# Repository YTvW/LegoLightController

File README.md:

# QBee LED Controller

A LEGO-stud-compatible LED controller board (Rev 1.0) built around the ATSAMD11C14A,
powered over USB-C. It drives up to two WS2812B (NeoPixel) strips and three
single-color LED channels.

## Hardware overview

| Part | Function |
|---|---|
| U1 — ATSAMD11C14A (SOIC-14) | MCU, 16KB flash / 4KB RAM, native USB |
| U2 — AP2111H-3.3 | 3.3V LDO for the MCU |
| P1 — USB-C (USB4110) | Power (5V) + USB 2.0 data; 5.1k CC pulldowns identify the board as a power sink |
| Q1–Q3 — BC847 | Low-side switches for the three LED channels (1k base, 10k pulldown) |
| R10, R11 — 470Ω | Series resistors on the WS2812B data lines |

### Connectors / IO

| Connector | Pads | Signal | MCU pin | Arduino pin |
|---|---|---|---|---|
| J1 | 1: +5V, 2: switched GND | LED1 channel | PA02 | 2 |
| J2 | 1: +5V, 2: switched GND | LED2 channel | PA04 | 4 |
| J3 | 1: +5V, 2: switched GND | LED3 channel | PA05 | 5 |
| J4 | 1: +5V, 2: data, 3: GND | WS2812B strip (DL1) | PA14 | 14 |
| J5 | 1: +5V, 2: data, 3: GND | WS2812B strip (DL2) | PA15 | 15 |
| J7 | 1: 3V3, 2: RESET, 3: SWCLK, 4: SWDIO, 5: NC, 6: GND | SWD programming header (DNP) | PA28/PA30/PA31 | — |
| TP1 | test point | EXT1 spare GPIO | PA08 | 8 |
| TP2 | test point | EXT2 spare GPIO | PA09 | 9 |

The LED channels (J1–J3) switch the LED's ground side through a transistor:
connect an LED (with its own series resistor if needed) between pad 1 (+5V)
and pad 2. A HIGH on the MCU pin turns the channel on.

Notes per pin:

- **PA02 (LED1, pin 2)** has no timer output — hardware PWM is not possible.
  `analogWrite()` on this pin uses the true 10-bit DAC; the transistor makes
  this behave as a crude analog dimmer only. Prefer channels LED2/LED3 for
  smooth PWM dimming.
- **PA04/PA05 (LED2/LED3)** have TC1 waveform outputs (WO0/WO1) — used by
  `pwm_driver` channels 0 and 1.
- **PA14/PA15 (strips)** also carry TC1 outputs; do not `analogWrite()` them.

## Arduino environment setup

1. Install the [Arduino IDE](https://www.arduino.cc/en/software) (2.x).
2. Add the Fab SAM core: **File → Preferences → Additional boards manager URLs**:

   ```
   https://raw.githubusercontent.com/qbolsee/ArduinoCore-fab-sam/master/json/package_Fab_SAM_index.json
   ```

3. **Tools → Board → Boards Manager**, search "Fab SAM", install
   **Fab SAM core for Arduino** (this project was built with 1.12.0).
4. Select **Tools → Board → Fab SAM boards → Generic D11C14A**.

### Board settings (Tools menu)

| Setting | Value | Notes |
|---|---|---|
| Clock Source | `INTERNAL_USB_CALIBRATED_OSCILLATOR` | Crystalless; calibrates 48MHz from USB. Switch to `INTERNAL_OSCILLATOR` if USB is disabled. |
| Bootloader Size | `4KB_BOOTLOADER` | Leaves 12KB for the application |
| Serial Config | `NO_UART_ONE_WIRE_ONE_SPI` | Saves ~1.5KB vs the default; USB `Serial` still works. The hardware UART (`Serial1`) is not wired to anything on this board. |
| USB Config | `CDC_ONLY` | Needed for `Serial` debugging and one-click uploads |
| Float | default | |
| Timer PWM Frequency | default (732.4Hz) | Only affects `analogWrite()` |

### Uploading

Normal uploads go over USB via the SAM-BA bootloader: just press Upload —
the IDE opens the port at 1200 baud to reset the board into the bootloader
automatically (this requires the running sketch to have USB CDC enabled).

If the chip is blank, or the sketch was built without CDC, flash via the SWD
pads (J7) with a CMSIS-DAP programmer and
[edbg](https://github.com/ataradov/edbg), or use the IDE's
*Burn Bootloader* with the Fab programmer selected. Once the bootloader is
on, USB uploads work as above.

## Firmware (`QBee Software/QBeeFirmware`)

| File | Purpose |
|---|---|
| `QBeeFirmware.ino` | Main sketch |
| `ws2812b_dma_driver.c/h` | WS2812B driver using **TCC0** PWM + DMA. Non-blocking: `ws2812b_show()` starts a hardware transfer and returns immediately. Uses TCC0's double-buffered `CCB` compare register so bit timing is glitch-free and immune to interrupts/USB load. |
| `pwm_driver.c/h` | LED-channel PWM using **TC1** (channels 0/1 → pins 4/5). TC2 exists but its outputs land on the SWD pins only. Costs no flash while unused (linker GC). |
| `neopixel_driver.c/h` | Older bit-banged WS2812B driver (blocks with interrupts off; superseded by the DMA driver) |

### Timer budget

| Peripheral | Owner |
|---|---|
| TCC0 | `ws2812b_dma_driver` (do not combine with `analogWrite`/`pwm_driver` on TCC0 pins) |
| TC1 | `pwm_driver` channels 0/1 (pins 4/5). Also claimed by `tone()` — don't use both. |
| TC2 | `pwm_driver` channels 2/3 — outputs only on SWD pins PA30/PA31, effectively unusable |
| SysTick | `millis()`/`micros()`/`delay()` (not a shared peripheral) |
| DMAC ch 0 | `ws2812b_dma_driver` |

### Flash budget

The app space is 12288 bytes. Measured levers if space runs out:

| Change | Approx. saving |
|---|---|
| Serial Config → `NO_UART...` | 1.5KB (free — `Serial1` unused) |
| USB Config → `WITHOUT_CDC` (drop `Serial` prints) | +2KB |
| USB Config → `USB_DISABLED` (also set Clock → `INTERNAL_OSCILLATOR`) | +4KB more |
| Bootloader → `NO_BOOTLOADER` (SWD uploads only) | +4KB of app space |

## Known hardware issues (Rev 1.0)

- **No level shifter on the WS2812B data lines.** Data is 3.3V while the
  strip runs at 5V; the strip's VIH spec is 0.7×VDD = 3.5V, so operation
  relies on real-world margin. Symptom: strips work on a USB-C wall supply
  but fail or glitch on some PC ports (slightly higher/noisier VBUS).
  Workaround: a silicon diode in series with the strip's +5V feed (drops
  strip VDD to ~4.4V). Proper fix for Rev 2: a 74AHCT1G125 / SN74LV1T125
  buffer on each data line, powered from 5V.
- **LED1 (PA02) has no hardware PWM** — see pin notes above.

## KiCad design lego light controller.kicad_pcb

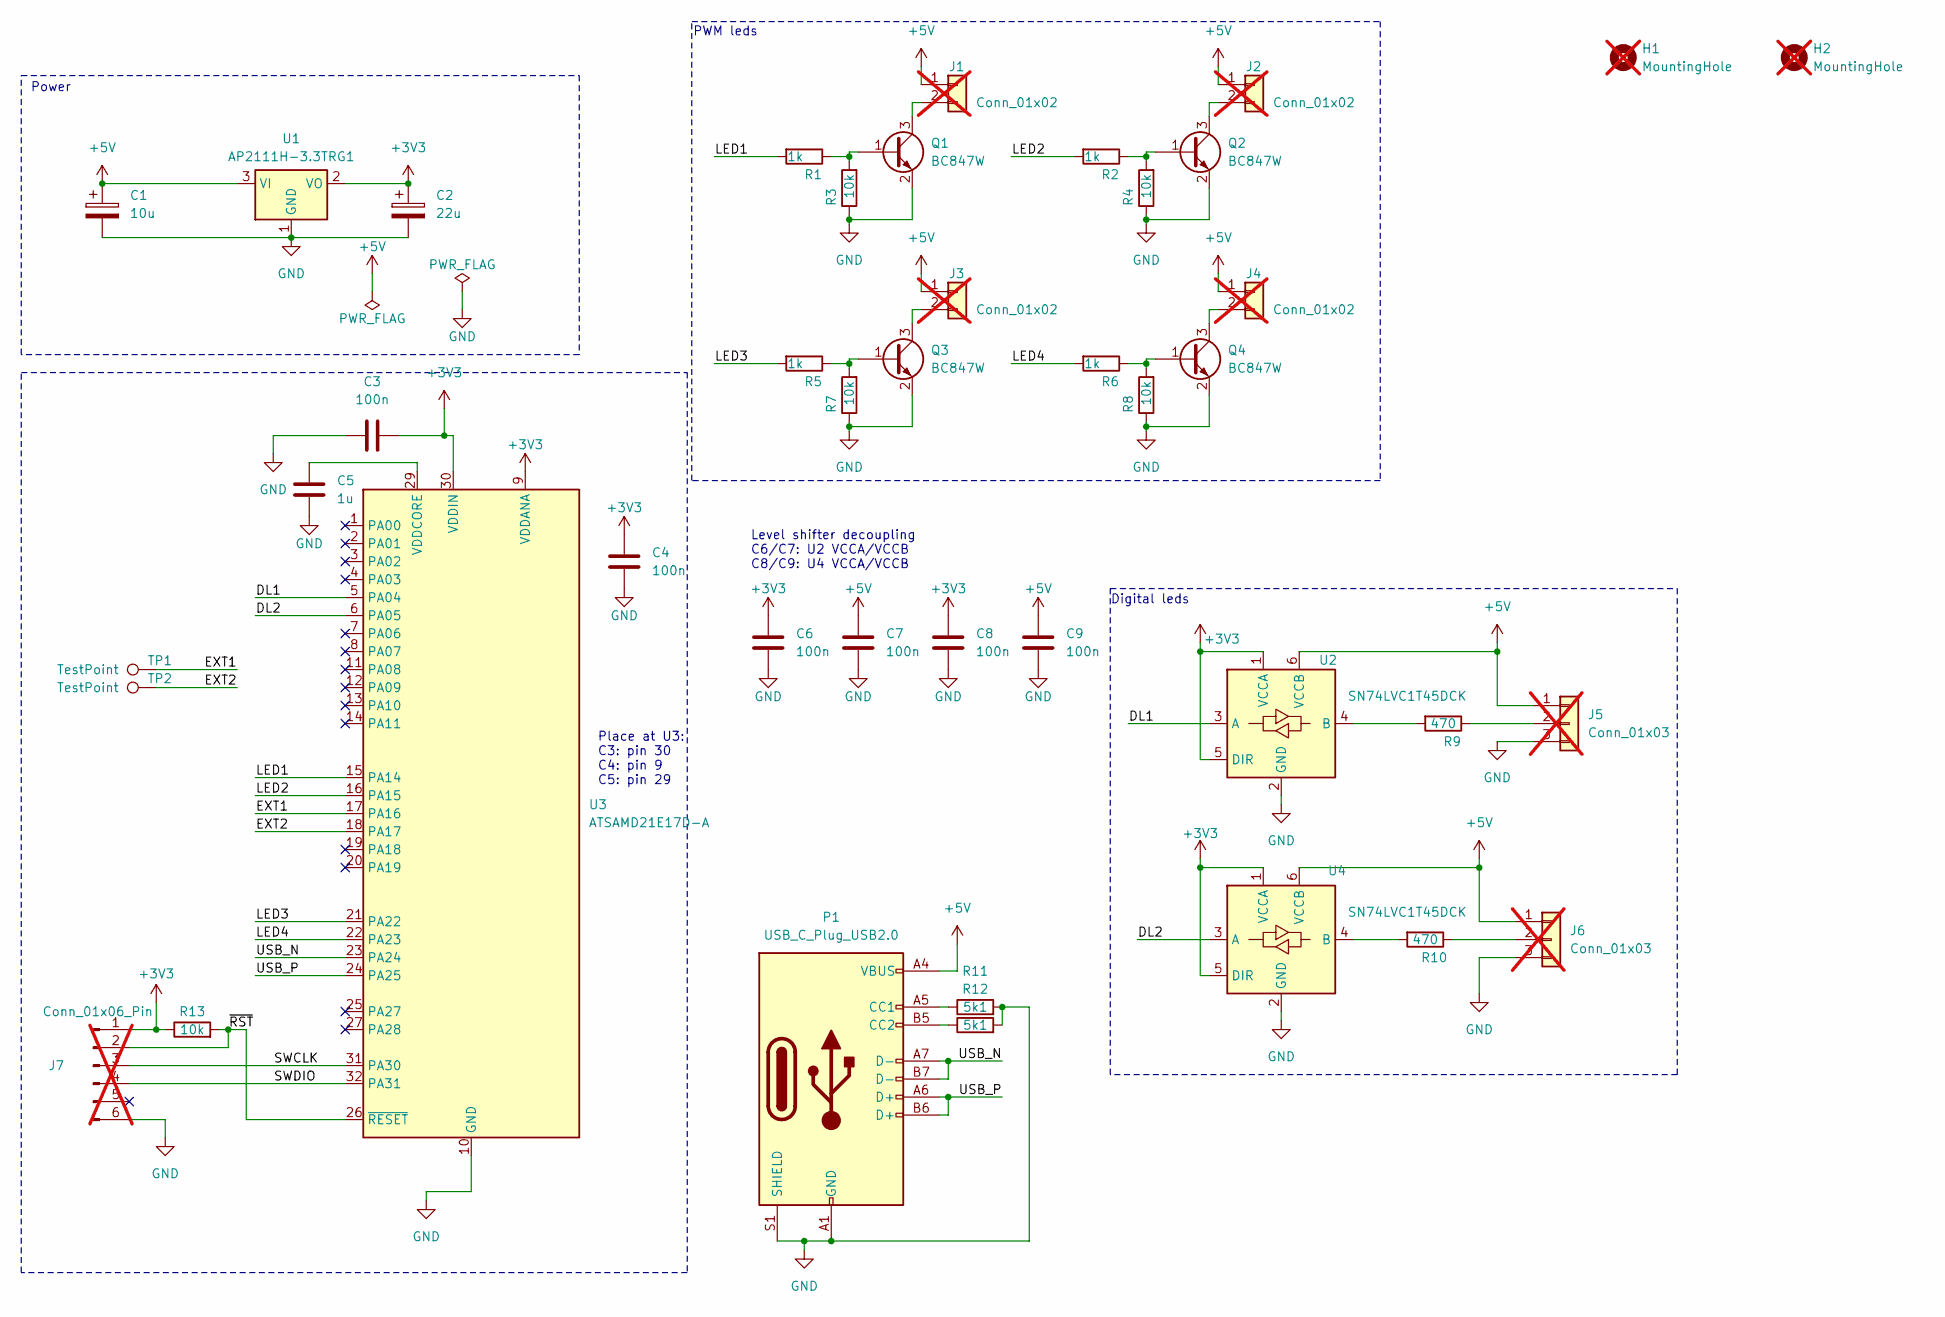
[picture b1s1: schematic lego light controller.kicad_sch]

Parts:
C1: 10u; CP_Elec_3x5.3; MPN 875105240001
C2: 22u; CP_Elec_3x5.3; MPN 875105240003
C3: 100n; C_0805_2012Metric
C4, C6, C7, C8, C9: 100n; C_0603_1608Metric
C5: 1u; C_0603_1608Metric
H1, H2: MountingHole; LEGO 4Studs; not fitted
J1, J2, J3, J4: Conn_01x02; PinHeader_1x02_P2.54mm_Vertical; not fitted
J5, J6: Conn_01x03; PinHeader_1x03_P2.54mm_Vertical; not fitted
J7: Conn_01x06_Pin; SW_DIP_SPSTx03_Slide_KingTek_DSHP03TJ_W5.25mm_P1.27mm_JPin; not fitted
P1: USB_C_Plug_USB2.0; USB_C_Receptacle_GCT_USB4110; MPN USB4110-GF-A
Q1, Q2, Q3, Q4: BC847W; SOT-23; MPN BC817-16LT3G
R1, R2, R5, R6: 1k; R_0603_1608Metric
R3, R4, R7, R8, R13: 10k; R_0603_1608Metric
R9, R10: 470; R_0603_1608Metric
R11, R12: 5k1; R_0603_1608Metric
TP1, TP2: TestPoint; TestPoint_Pad_2.0x2.0mm
U1: AP2111H-3.3TRG1; SOT-223-3_TabPin2; MPN AP2111H-3.3TRG1
U2, U4: SN74LVC1T45DCK; SOT-363_SC-70-6
U3: ATSAMD21E17D-A; TQFP-32_7x7mm_P0.8mm

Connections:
+3V3: C2.1, C3.2, C4.1, C6.1, C8.1, J7.1, R13.1, U1.2 (VO), U2.1 (VCCA), U2.5 (DIR), U3.9 (VDDANA), U3.30 (VDDIN), U4.1 (VCCA), U4.5 (DIR)
+5V: C1.1, C7.1, C9.1, J1.1, J2.1, J3.1, J4.1, J5.1, J6.1, P1.A4 (VBUS), P1.A9 (VBUS), P1.B4 (VBUS), P1.B9 (VBUS), U1.3 (VI), U2.6 (VCCB), U4.6 (VCCB)
/DL1: U2.3 (A), U3.5 (PA04)
/DL2: U3.6 (PA05), U4.3 (A)
/EXT1: TP1.1 (1_1), U3.17 (PA16)
/EXT2: TP2.1 (1_1), U3.18 (PA17)
/LED1: R1.2, U3.15 (PA14)
/LED2: R2.2, U3.16 (PA15)
/LED3: R5.2, U3.21 (PA22)
/LED4: R6.2, U3.22 (PA23)
/SWCLK: J7.3, U3.31 (PA30)
/SWDIO: J7.4, U3.32 (PA31)
/USB_N: P1.A7 (D-), P1.B7 (D-), U3.23 (PA24)
/USB_P: P1.A6 (D+), P1.B6 (D+), U3.24 (PA25)
/~RST: J7.2, R13.2, U3.26 (~RESET)
GND: C1.2, C2.2, C3.1, C4.2, C5.2, C6.2, C7.2, C8.2, C9.2, J5.3, J6.3, J7.6, P1.A1 (GND), P1.A12 (GND), P1.B1 (GND), P1.B12 (GND), P1.S1 (SHIELD), Q1.2 (E), Q2.2 (E), Q3.2 (E), Q4.2 (E), R3.1, R4.1, R7.1, R8.1, R11.2, R12.2, U1.1 (GND), U2.2 (GND), U3.10 (GND), U3.28 (GND), U4.2 (GND)
unnamed: J1.2, Q1.3 (C)
unnamed: J2.2, Q2.3 (C)
unnamed: J3.2, Q3.3 (C)
unnamed: J4.2, Q4.3 (C)
unnamed: J5.2, R9.1
unnamed: J6.2, R10.1
unnamed: P1.A5 (CC1), R11.1
unnamed: P1.B5 (CC2), R12.1
unnamed: Q1.1 (B), R1.1, R3.2
unnamed: Q2.1 (B), R2.1, R4.2
unnamed: Q3.1 (B), R5.1, R7.2
unnamed: Q4.1 (B), R6.1, R8.2
unnamed: R9.2, U2.4 (B)
unnamed: C5.1, U3.29 (VDDCORE)
unnamed: R10.2, U4.4 (B)

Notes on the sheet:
Power
PWM leds
Digital leds
Place at U3: C3: pin 30 C4: pin 9 C5: pin 29
Level shifter decoupling C6/C7: U2 VCCA/VCCB C8/C9: U4 VCCA/VCCB

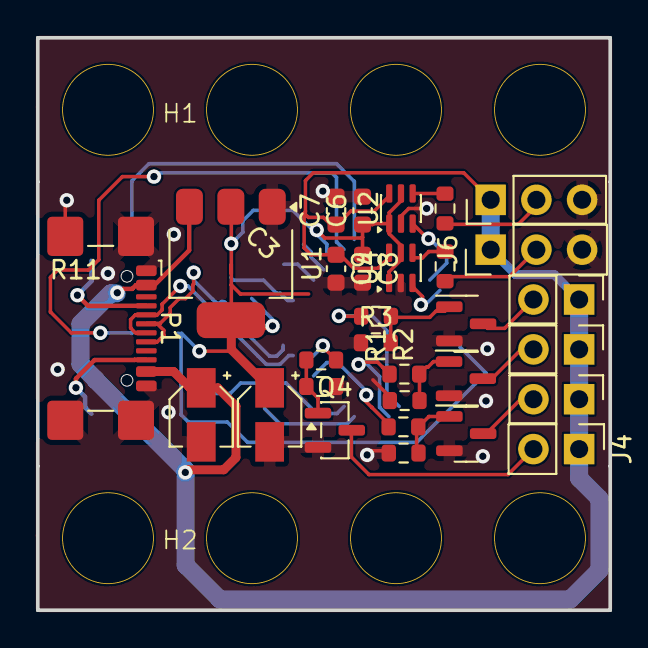
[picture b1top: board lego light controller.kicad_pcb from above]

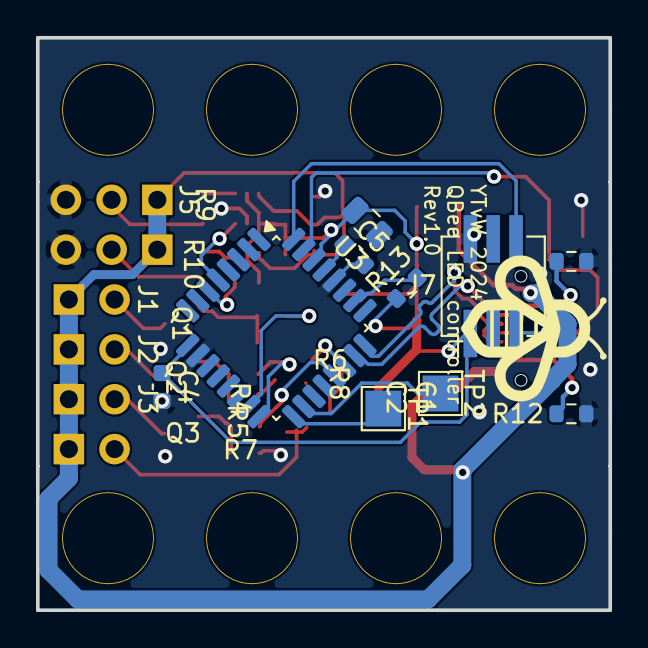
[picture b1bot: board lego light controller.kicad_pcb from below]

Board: 2 copper layers, 31.8 x 31.8 mm, 42 parts (10 on the bottom side), 31 nets.

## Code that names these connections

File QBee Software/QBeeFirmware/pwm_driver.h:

/**
 * @file pwm_driver.h
 * @brief TC-based PWM driver for SAMD11C / SAMD21
 *
 * Uses two TC hardware peripherals for efficient PWM generation,
 * leaving TCC0 free for the WS2812B DMA driver. The chip is selected
 * automatically at compile time.
 *
 * Channel to pin mapping on the SAMD11C14A (TC1/TC2):
 *   - Channel 0: PA04 (TC1/WO[0]) or PA14
 *   - Channel 1: PA05 (TC1/WO[1]) or PA15
 *   - Channel 2: PA30 (TC2/WO[0]) - SWCLK programming pin!
 *   - Channel 3: PA31 (TC2/WO[1]) - SWDIO programming pin!
 *
 * PA14/PA15 are normally taken by the WS2812B strips, and channels 2/3
 * sacrifice the SWD debug port, so PA04 and PA05 are the practical choices.
 *
 * Channel to pin mapping on the SAMD21 (TC3/TC4):
 *   - Channel 0: PA14 (TC3/WO[0]) or PA18
 *   - Channel 1: PA15 (TC3/WO[1]) or PA19
 *   - Channel 2: PA22 (TC4/WO[0]) or PB08 (G/J parts)
 *   - Channel 3: PA23 (TC4/WO[1]) or PB09 (G/J parts)
 *
 * Note: pwm_deinit() on the SAMD21 also gates the GCLK channels shared
 * with TCC2 and TC5 (which analogWrite may be using on their pins).
 *
 * TC counters run in 8-bit mode, so the PWM frequency range is
 * ~184Hz to ~188kHz (out-of-range requests are clamped).
 */

#ifndef PWM_DRIVER_H
#define PWM_DRIVER_H

#include <Arduino.h>
#include <sam.h>

#ifdef __cplusplus
extern "C" {
#endif

// PWM configuration
#define PWM_RESOLUTION_BITS   8
#define PWM_MAX_VALUE         ((1 << PWM_RESOLUTION_BITS) - 1)  // 255 for 8-bit
#define PWM_DEFAULT_FREQ_HZ   1000

// Channel indices
#define PWM_CHANNEL_0   0
#define PWM_CHANNEL_1   1
#define PWM_CHANNEL_2   2
#define PWM_CHANNEL_3   3
#define PWM_NUM_CHANNELS 4

/**
 * @brief PWM channel configuration structure
 */
typedef struct {
    uint8_t pin;           // Arduino pin number
    uint8_t portPin;       // Port pin (PA number)
    uint8_t wo;            // Waveform output number (0-3 or 4-7 for inverted)
    uint8_t muxFunction;   // PMUX function (E or F typically for TCC)
} pwm_channel_config_t;

/**
 * @brief Initialize the TC1/TC2 PWM driver
 *
 * @param frequencyHz PWM frequency in Hz (e.g., 1000 for 1kHz)
 * @return true if initialization successful, false otherwise
 */
bool pwm_init(uint32_t frequencyHz);

/**
 * @brief Configure a specific pin for PWM output
 * 
 * @param channel Channel index (0-3)
 * @param pin Arduino pin number
 * @return true if configuration successful, false if pin not supported
 */
bool pwm_configure_channel(uint8_t channel, uint8_t pin);

/**
 * @brief Set the duty cycle for a PWM channel
 * 
 * @param channel Channel index (0-3)
 * @param duty Duty cycle (0 to PWM_MAX_VALUE, i.e., 0-255 for 8-bit)
 */
void pwm_set_duty(uint8_t channel, uint16_t duty);

/**
 * @brief Set duty cycle as a percentage
 * 
 * @param channel Channel index (0-3)
 * @param percent Duty cycle percentage (0.0 to 100.0)
 */
void pwm_set_duty_percent(uint8_t channel, float percent);

/**
 * @brief Enable PWM output on a channel
 * 
 * @param channel Channel index (0-3)
 */
void pwm_enable_channel(uint8_t channel);

/**
 * @brief Disable PWM output on a channel (output goes low)
 * 
 * @param channel Channel index (0-3)
 */
void pwm_disable_channel(uint8_t channel);

/**
 * @brief Get current duty cycle value for a channel
 * 
 * @param channel Channel index (0-3)
 * @return Current duty cycle value
 */
uint16_t pwm_get_duty(uint8_t channel);

/**
 * @brief Set PWM frequency (affects all channels)
 * 
 * @param frequencyHz New frequency in Hz
 */
void pwm_set_frequency(uint32_t frequencyHz);

/**
 * @brief Deinitialize the PWM driver and release resources
 */
void pwm_deinit(void);

#ifdef __cplusplus
}
#endif

#endif // PWM_DRIVER_H

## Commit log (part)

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2024-02-17 add progress so far
2024-02-17 make schema neat
2024-02-18 add values and update usb c
2024-02-18 update project
2024-02-19 add logo
2024-02-19 change logo size
2024-02-19 update gitignore
2024-02-19 clean up pcb
2024-02-19 fix trace to moved component
2024-02-19 fix track to 3v3 outpu
2024-02-21 update footprints and redo layout
2024-02-22 move usb to center
2024-02-22 add pads to unused io
2024-02-26 update to kicad v8
2024-02-26 fix pcb name
2024-02-26 fix BOM
2026-06-20 small fixes
